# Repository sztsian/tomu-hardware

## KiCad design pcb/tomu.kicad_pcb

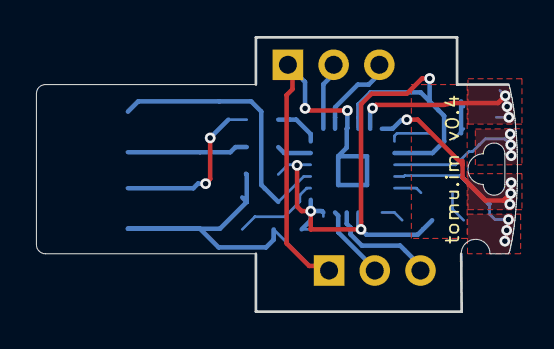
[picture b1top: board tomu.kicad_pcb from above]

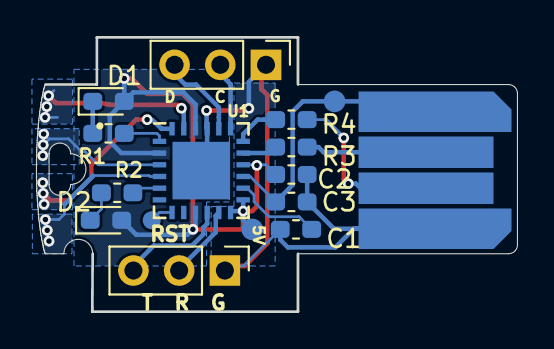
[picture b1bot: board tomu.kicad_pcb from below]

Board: 2 copper layers, 26.7 x 15.2 mm, 17 parts (16 on the bottom side), 17 nets.

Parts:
C1, C2: 1uF, 10V, X5R, 0402; C_0603_1608Metric_Pad1.05x0.95mm_HandSolder
C3: 4.7uF, 6.3V, X5R, 0402; C_0603_1608Metric_Pad1.05x0.95mm_HandSolder
D1: LED Green 0402; LED_0603_1608Metric_Pad1.05x0.95mm_HandSolder
D2: LED, Red, 0402; LED_0603_1608Metric_Pad1.05x0.95mm_HandSolder
P1: USART0; PinHeader_1x03_P2.54mm_Vertical
P2: DEBUG; PinHeader_1x03_P2.54mm_Vertical
P3: USB-PCB
P4: RESET_PAD; pads-1x1
P5: 5V_PAD; pads-1x1
P6: 3V_PAD; pads-1x1
R1, R2: 100 Ohm, 1%, 1/16W, 0402; R_0603_1608Metric_Pad1.05x0.95mm_HandSolder
R3, R4: 15 Ohm, 1%, 1/16W, 0402; R_0603_1608Metric_Pad1.05x0.95mm_HandSolder
U1: EFM32HG309; QFN-24-1EP_5x5mm_Pitch0.65mm
XX1: Button solder mask removal; soldermask-removal

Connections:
+3V3: C2.1, D1.2, D2.2, P6.1, U1.2, U1.9, U1.12, U1.13, U1.16, U1.22
//RESET: P4.1, U1.7
/DBG_SWCLK: P2.2, U1.19
/DBG_SWDIO: P2.3, U1.20
/DEC: C1.2, U1.14
/LED0: R2.2, U1.5
/LED1: R1.1, U1.1
/LEU0_RX: P1.2, U1.11
/LEU0_TX: P1.3, U1.10
/RUSB_D+: R4.2, U1.18
/RUSB_D-: R3.2, U1.17
/USB_5V: C3.1, P3.1, P5.1, U1.15
/USB_D+: P3.3, R4.1
/USB_D-: P3.2, R3.1
GND: C1.1, C2.2, C3.2, P1.1, P2.1, P3.4, U1.21, U1.25
unnamed: D1.1, R1.2
unnamed: D2.1, R2.1

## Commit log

2019-07-13 Add 2.54 pinhead version for easy developing

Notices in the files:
pcb/tomu.kicad_pcb:
License: CC-BY-SA 4.0 or TAPR
